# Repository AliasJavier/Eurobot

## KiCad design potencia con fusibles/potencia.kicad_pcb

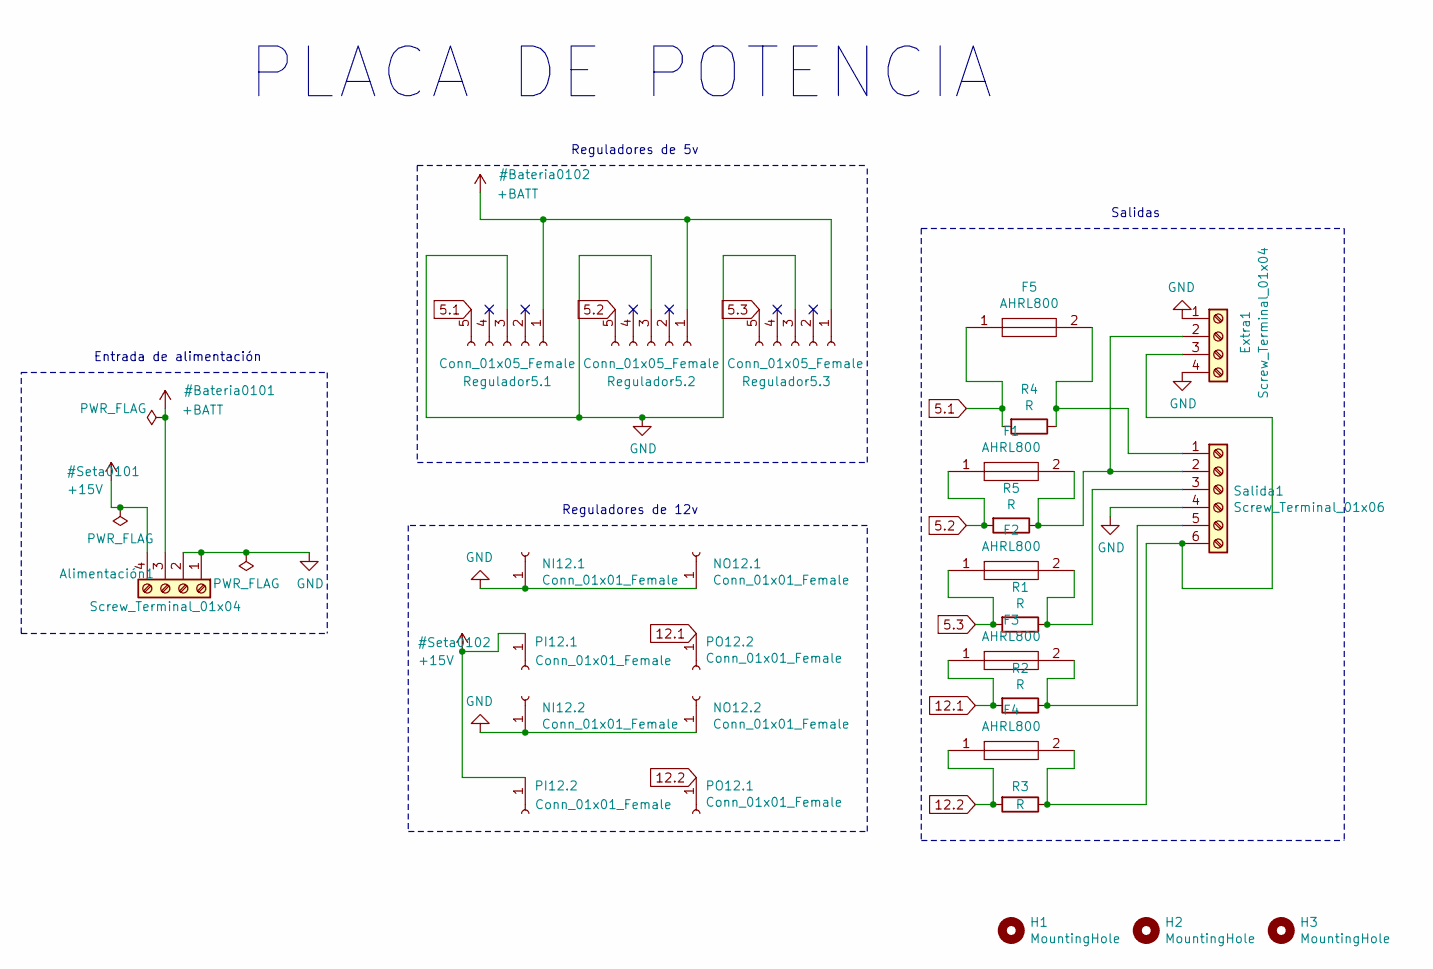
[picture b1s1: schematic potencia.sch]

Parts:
Alimentación1: Screw_Terminal_01x04; Conector_4p_5.08
Extra1: Screw_Terminal_01x04; Conector_4p_5.08
F1, F2, F3, F4, F5: AHRL800; AHRL800AP; Mouser Part Number 650-AHRL800
H1, H2, H3: MountingHole; MountingHole_3.2mm_M3_ISO7380
NI12.1, NI12.2: Conn_01x01_Female; PinSocket_1x01_P2.54mm_Vertical
NO12.1, NO12.2: Conn_01x01_Female; PinSocket_1x01_P2.54mm_Vertical
PI12.1, PI12.2: Conn_01x01_Female; PinSocket_1x01_P2.54mm_Vertical
PO12.1, PO12.2: Conn_01x01_Female; PinSocket_1x01_P2.54mm_Vertical
R1, R2, R3, R4, R5: R; R_Axial_DIN0204_L3.6mm_D1.6mm_P5.08mm_Horizontal
Regulador5.1, Regulador5.2, Regulador5.3: Conn_01x05_Female; PinSocket_1x05_P2.54mm_Vertical
Salida1: Screw_Terminal_01x06; Conector_6p_5.08

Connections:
5.1: F5.1, R4.2, Regulador5.1.5
5.2: F1.1, R5.2, Regulador5.2.5
5.3: F2.1, R1.2, Regulador5.3.5
12.1: F3.1, PO12.2.1, R2.2
12.2: F4.1, PO12.1.1, R3.2
+15V: Alimentación1.4, PI12.1.1, PI12.2.1
+BATT: Alimentación1.3, Regulador5.1.1, Regulador5.2.1, Regulador5.3.1
GND: Alimentación1.1, Alimentación1.2, Extra1.1, Extra1.4, NI12.1.1, NI12.2.1, NO12.1.1, NO12.2.1, Regulador5.1.3, Regulador5.2.3, Regulador5.3.3, Salida1.4
unnamed: Extra1.2, F1.2, R5.1, Salida1.2
unnamed: Extra1.3, F4.2, R3.1, Salida1.6
unnamed: F2.2, R1.1, Salida1.3
unnamed: F3.2, R2.1, Salida1.5
unnamed: F5.2, R4.1, Salida1.1

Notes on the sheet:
Entrada de alimentación
Reguladores de 5v
Reguladores de 12v
Salidas
PLACA DE POTENCIA

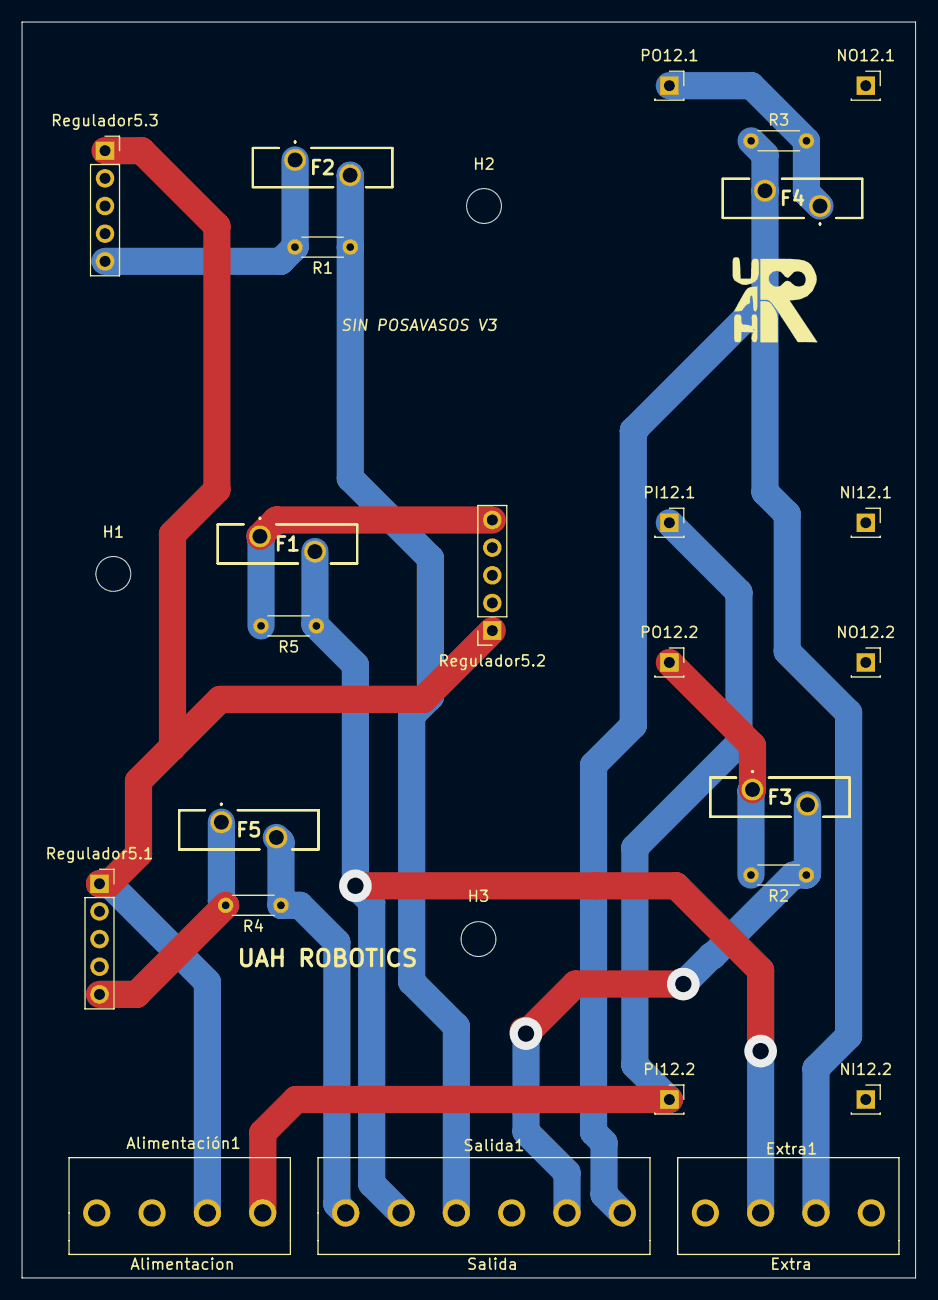
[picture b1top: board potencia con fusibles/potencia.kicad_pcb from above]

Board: 2 copper layers, 82.0 x 115.3 mm, 27 parts (0 on the bottom side), 13 nets.

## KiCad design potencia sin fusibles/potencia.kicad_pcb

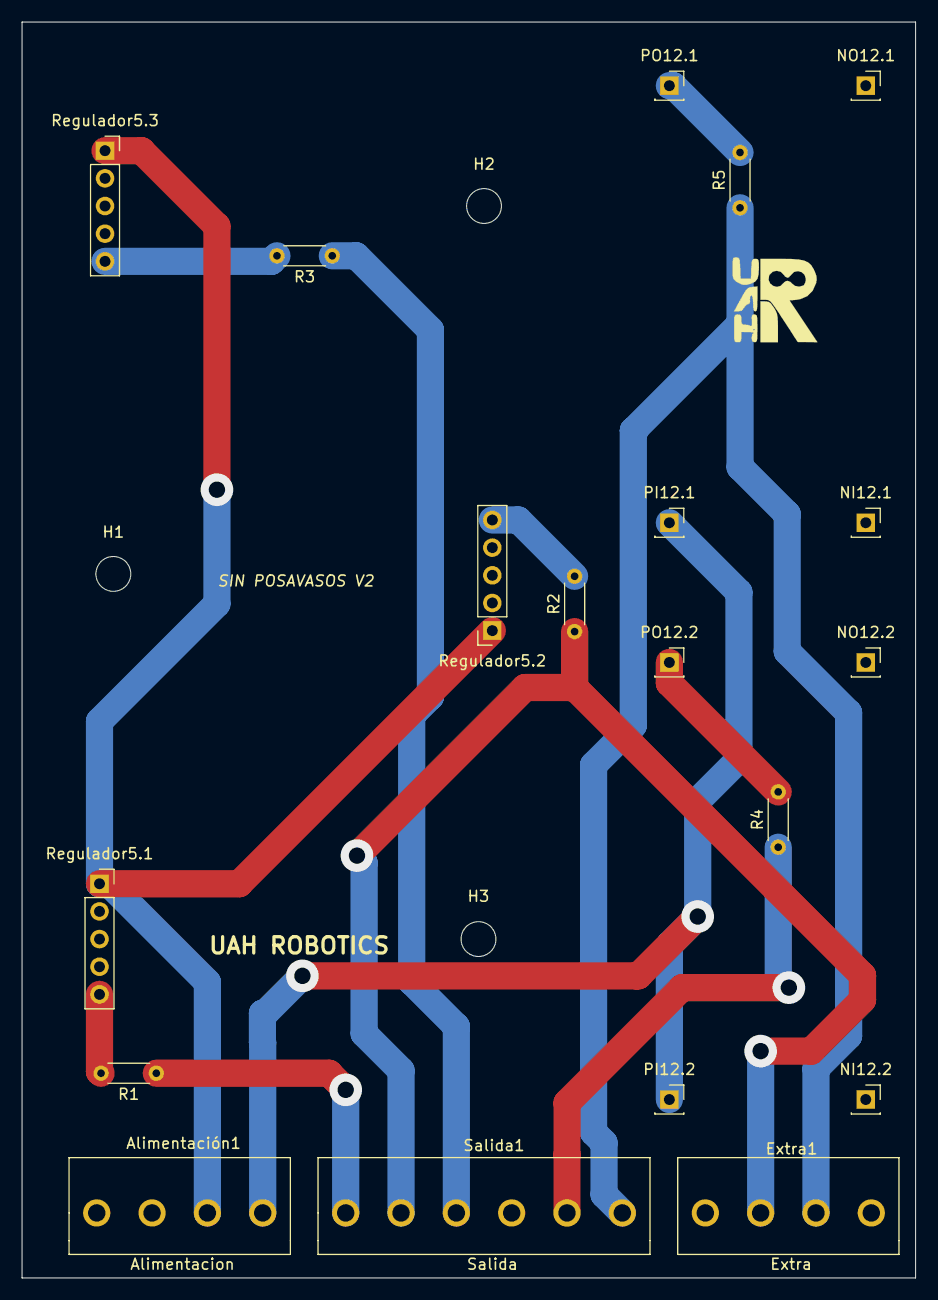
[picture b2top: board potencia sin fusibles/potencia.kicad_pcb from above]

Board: 2 copper layers, 82.0 x 115.3 mm, 22 parts (0 on the bottom side), 13 nets.

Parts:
Alimentación1: Screw_Terminal_01x04; Conector_4p_5.08
Extra1: Screw_Terminal_01x04; Conector_4p_5.08
H1, H2, H3: MountingHole; MountingHole_3.2mm_M3_ISO7380
NI12.1, NI12.2: Conn_01x01_Female; PinSocket_1x01_P2.54mm_Vertical
NO12.1, NO12.2: Conn_01x01_Female; PinSocket_1x01_P2.54mm_Vertical
PI12.1, PI12.2: Conn_01x01_Female; PinSocket_1x01_P2.54mm_Vertical
PO12.1, PO12.2: Conn_01x01_Female; PinSocket_1x01_P2.54mm_Vertical
R1, R2, R3, R4, R5: R; R_Axial_DIN0204_L3.6mm_D1.6mm_P5.08mm_Horizontal
Regulador5.1, Regulador5.2, Regulador5.3: Conn_01x05_Female; PinSocket_1x05_P2.54mm_Vertical
Salida1: Screw_Terminal_01x06; Conector_6p_5.08

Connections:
5.1: R1.2, Regulador5.1.5
5.2: R2.2, Regulador5.2.5
5.3: R3.2, Regulador5.3.5
12.1: PO12.2.1, R4.2
12.2: PO12.1.1, R5.2
+15V: Alimentación1.4, PI12.1.1, PI12.2.1
+BATT: Alimentación1.3, Regulador5.1.1, Regulador5.2.1, Regulador5.3.1
GND: Alimentación1.1, Alimentación1.2, Extra1.1, Extra1.4, NI12.1.1, NI12.2.1, NO12.1.1, NO12.2.1, Regulador5.1.3, Regulador5.2.3, Regulador5.3.3, Salida1.4
unnamed: Extra1.2, R2.1, Salida1.2
unnamed: Extra1.3, R5.1, Salida1.6
unnamed: R1.1, Salida1.1
unnamed: R3.1, Salida1.3
unnamed: R4.1, Salida1.5

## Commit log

2021-03-19 primero
2021-05-27 version v2
2021-05-27 con fusibles
2021-05-30 final
